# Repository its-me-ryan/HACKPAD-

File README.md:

# Ryan's HACKPAD
Hackpad is an 8-key macropad with dual rotary encoders and per-key RGB lighting and uses QMK Firmware.

# Features

- Two-part custom 3D-printed case designed in Fusion 360 — clean, compact, and fits together perfectly.

- 8 mechanical keys (MX-compatible) arranged in a 3×3 layout.

- Dual EC11 rotary encoders — one for volume, one for anything else you want.

- 10 SK6812-MINI-E RGB LEDs — fully addressable per-key lighting + underglow.

- XIAO RP2040 at the heart of it all: tiny, powerful, easy to flash.

- Diode-isolated switch matrix for clean scanning and ghost-free operation.

- Designed for QMK (but fully functional via RP2040 firmware).

- Compact footprint with screw-mounting support at all 4 corners.

- Custom PCB laid out manually in KiCad (with GND pour!).

And yes — it looks awesome. 😎

# CAD Model

The enclosure is split into two printed parts:
- Bottom shell (supports the PCB and holds heat-set inserts.)
- Top plate (holds the switches and encoders in perfect alignment)
- Everything assembles using M2 screws and heat-set inserts.
- The entire case was modeled in Fusion 360, with careful tolerances for switch fitment and encoder height.
- The PCB was imported into Fusion to ensure perfect alignment between the switch cutouts, encoder holes, and standoffs.

# PCB
Here’s the PCB!
- Designed entirely in KiCad, routed by hand, and cleaned with a tidy GND pour.
- MX_V2 footprints for the switches
- Proper diode matrix for 8 keys
- 10 RGB LEDs chained neatly around the pad
- Footprints for two EC11 encoders
- XIAO RP2040 header footprint
- Clean, functional silkscreen and mounting holes
This was my first full custom PCB and it turned out great!
Schematics: 
PCB : 

# BOM
Required

- 8× MX-compatible switches

- 8× Keycaps

- 8× 1N4148 diodes (for matrix)

- 10× SK6812-MINI-E RGB LEDs

-  2× EC11 rotary encoders (with push switch)

- 1× Seeed Studio XIAO RP2040

- 1× Custom PCB

- 1× 3D printed case (top + bottom shells)

- 4× M2 heat-set inserts

- 4× M2 screws for case assembly

Optional / Not Used in This Build

- 0.1 µF capacitor (recommended for LED stability but optional)

- 1 µF capacitor (optional, also for LED power smoothing)

- OLED display (not included in this design but could be added in a future revision)
# EXTRA STUFF
- First time using KiCAD and Fusion 360. I had to revise the model 5 times before I got 0 Errors
- Making this during exam time, so wish me luck!
- Google is actually a lifesaver

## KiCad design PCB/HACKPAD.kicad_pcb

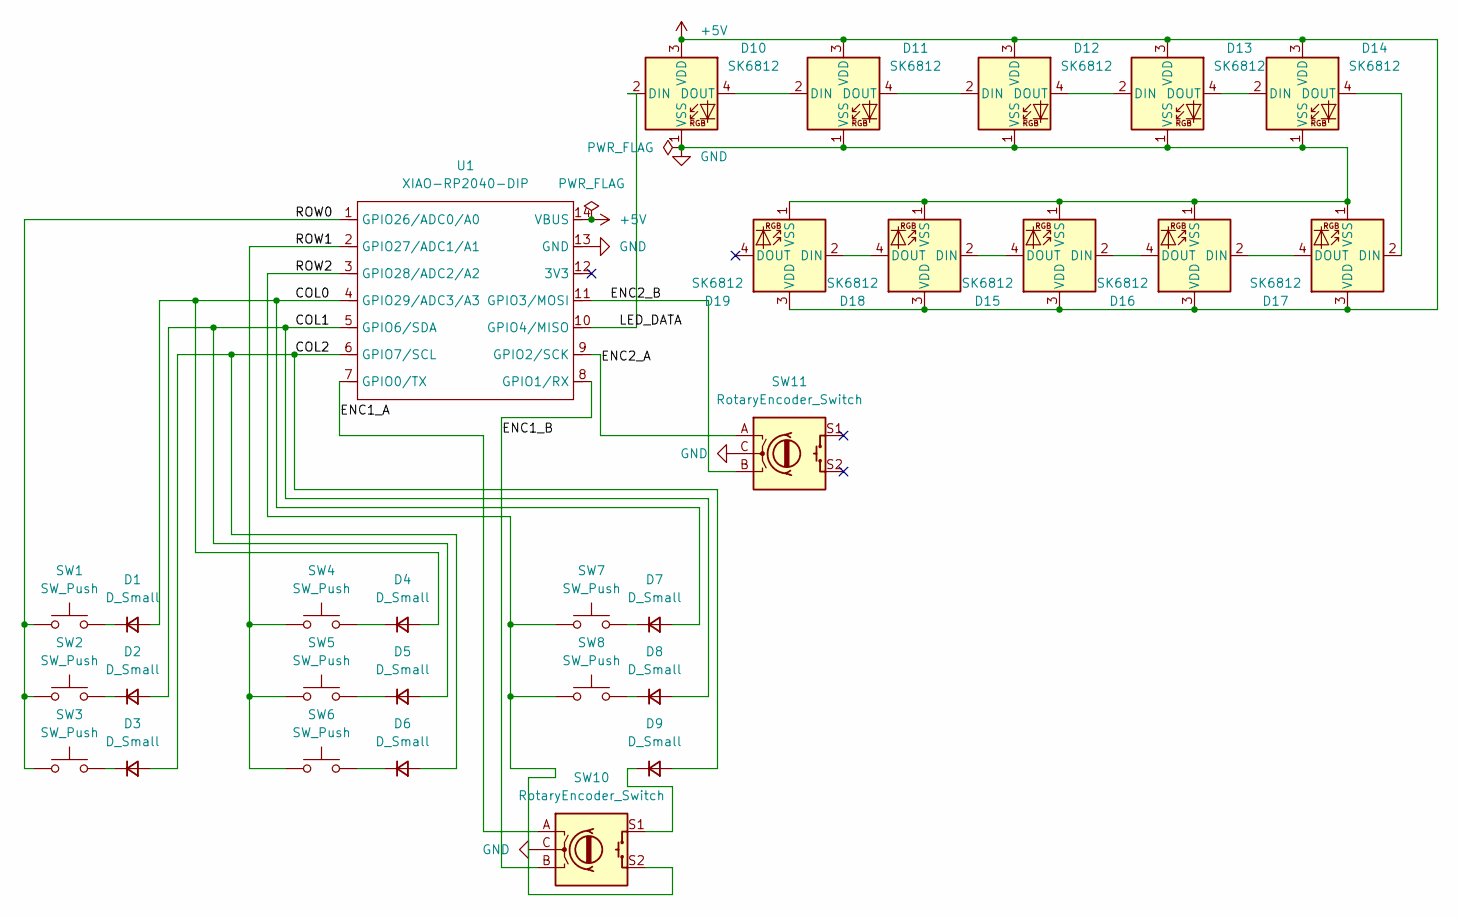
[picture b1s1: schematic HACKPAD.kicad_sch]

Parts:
D1, D2, D3, D4, D5, D6, D7, D8, D9: D_Small; D_DO-35_SOD27_P7.62mm_Horizontal
D10, D11, D12, D13, D14, D15, D16, D17, D18, D19: SK6812; LED_SK6812_PLCC4_5.0x5.0mm_P3.2mm
SW1, SW2, SW3, SW4, SW5, SW6, SW7, SW8: SW_Push; SW_Cherry_MX_1.00u_PCB
SW10, SW11: RotaryEncoder_Switch; RotaryEncoder_Alps_EC11E-Switch_Vertical_H20mm
U1: XIAO-RP2040-DIP

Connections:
+5V: D10.3 (VDD), D11.3 (VDD), D12.3 (VDD), D13.3 (VDD), D14.3 (VDD), D15.3 (VDD), D16.3 (VDD), D17.3 (VDD), D18.3 (VDD), D19.3 (VDD), U1.14 (VBUS)
/COL0: D1.2 (A), D4.2 (A), D7.2 (A), U1.4 (GPIO29/ADC3/A3)
/COL1: D2.2 (A), D5.2 (A), D8.2 (A), U1.5 (GPIO6/SDA)
/COL2: D3.2 (A), D6.2 (A), D9.2 (A), U1.6 (GPIO7/SCL)
/ENC1_A: SW10.A, U1.7 (GPIO0/TX)
/ENC1_B: SW10.B, U1.8 (GPIO1/RX)
/ENC2_A: SW11.A, U1.9 (GPIO2/SCK)
/ENC2_B: SW11.B, U1.11 (GPIO3/MOSI)
/LED_DATA: D10.2 (DIN), U1.10 (GPIO4/MISO)
/ROW0: SW1.1, SW2.1, SW3.1, U1.1 (GPIO26/ADC0/A0)
/ROW1: SW4.1, SW5.1, SW6.1, U1.2 (GPIO27/ADC1/A1)
/ROW2: SW7.1, SW8.1, SW10.S2, U1.3 (GPIO28/ADC2/A2)
GND: D10.1 (VSS), D11.1 (VSS), D12.1 (VSS), D13.1 (VSS), D14.1 (VSS), D15.1 (VSS), D16.1 (VSS), D17.1 (VSS), D18.1 (VSS), D19.1 (VSS), SW10.C, SW11.C, U1.13 (GND)
unnamed: D1.1 (K), SW1.2
unnamed: D2.1 (K), SW2.2
unnamed: D3.1 (K), SW3.2
unnamed: D4.1 (K), SW4.2
unnamed: D5.1 (K), SW5.2
unnamed: D6.1 (K), SW6.2
unnamed: D7.1 (K), SW7.2
unnamed: D8.1 (K), SW8.2
unnamed: D9.1 (K), SW10.S1
unnamed: D10.4 (DOUT), D11.2 (DIN)
unnamed: D11.4 (DOUT), D12.2 (DIN)
unnamed: D12.4 (DOUT), D13.2 (DIN)
unnamed: D13.4 (DOUT), D14.2 (DIN)
unnamed: D14.4 (DOUT), D17.2 (DIN)
unnamed: D15.2 (DIN), D16.4 (DOUT)
unnamed: D15.4 (DOUT), D18.2 (DIN)
unnamed: D16.2 (DIN), D17.4 (DOUT)
unnamed: D18.4 (DOUT), D19.2 (DIN)

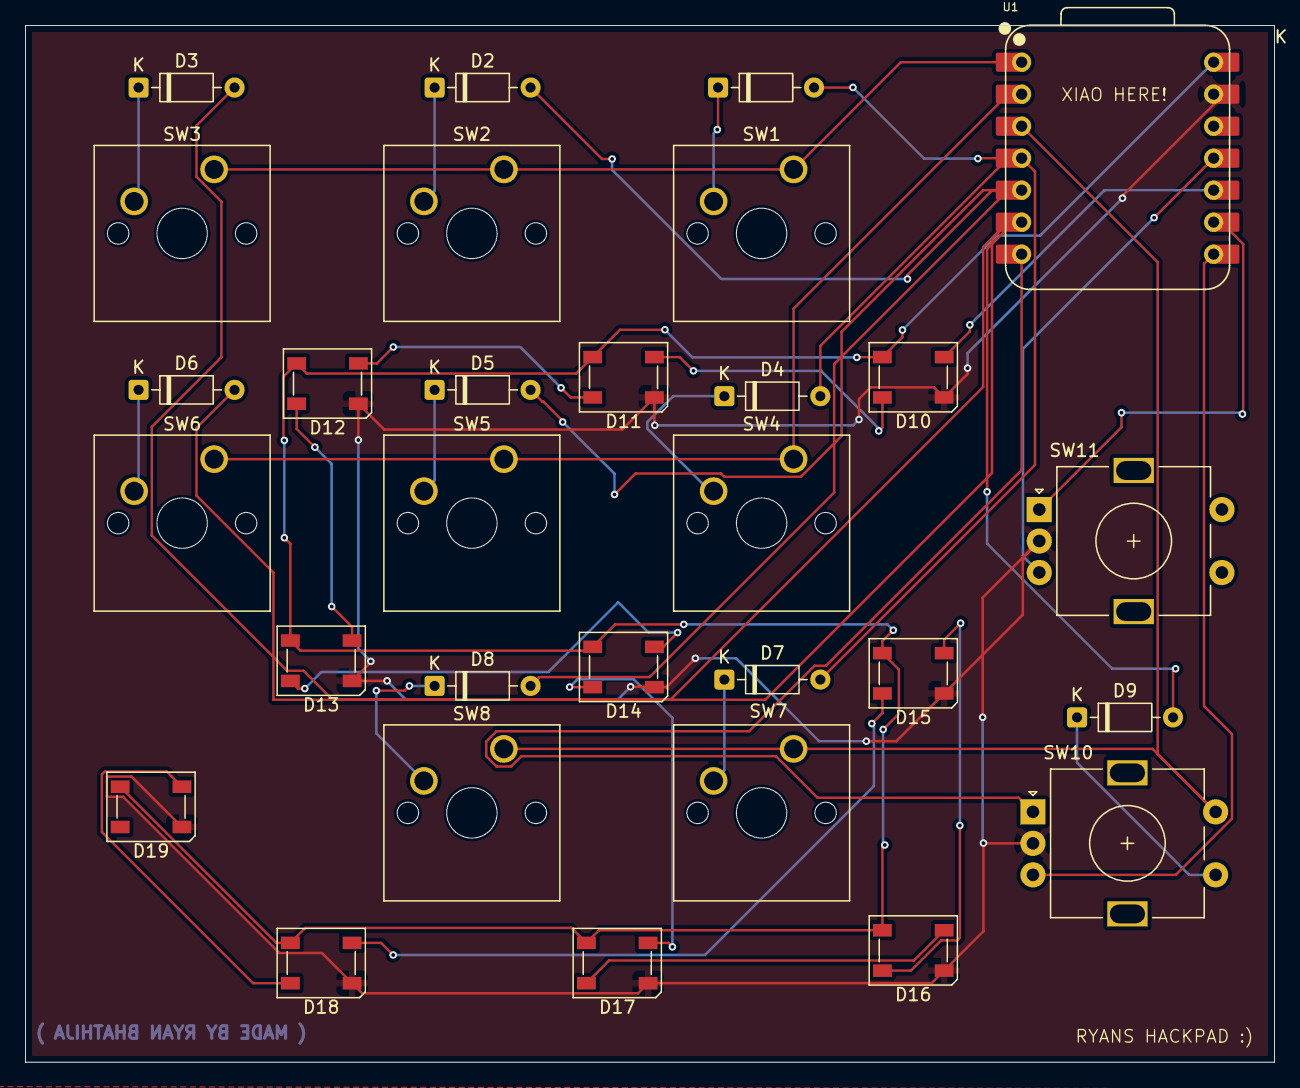
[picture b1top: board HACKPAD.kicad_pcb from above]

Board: 2 copper layers, 99.2 x 82.3 mm, 30 parts (0 on the bottom side), 31 nets.

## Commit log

2025-12-11 Update README with project details and specifications
    Added detailed project description, features, CAD model, PCB design, BOM, and extra notes for Ryan's Hackpad.
